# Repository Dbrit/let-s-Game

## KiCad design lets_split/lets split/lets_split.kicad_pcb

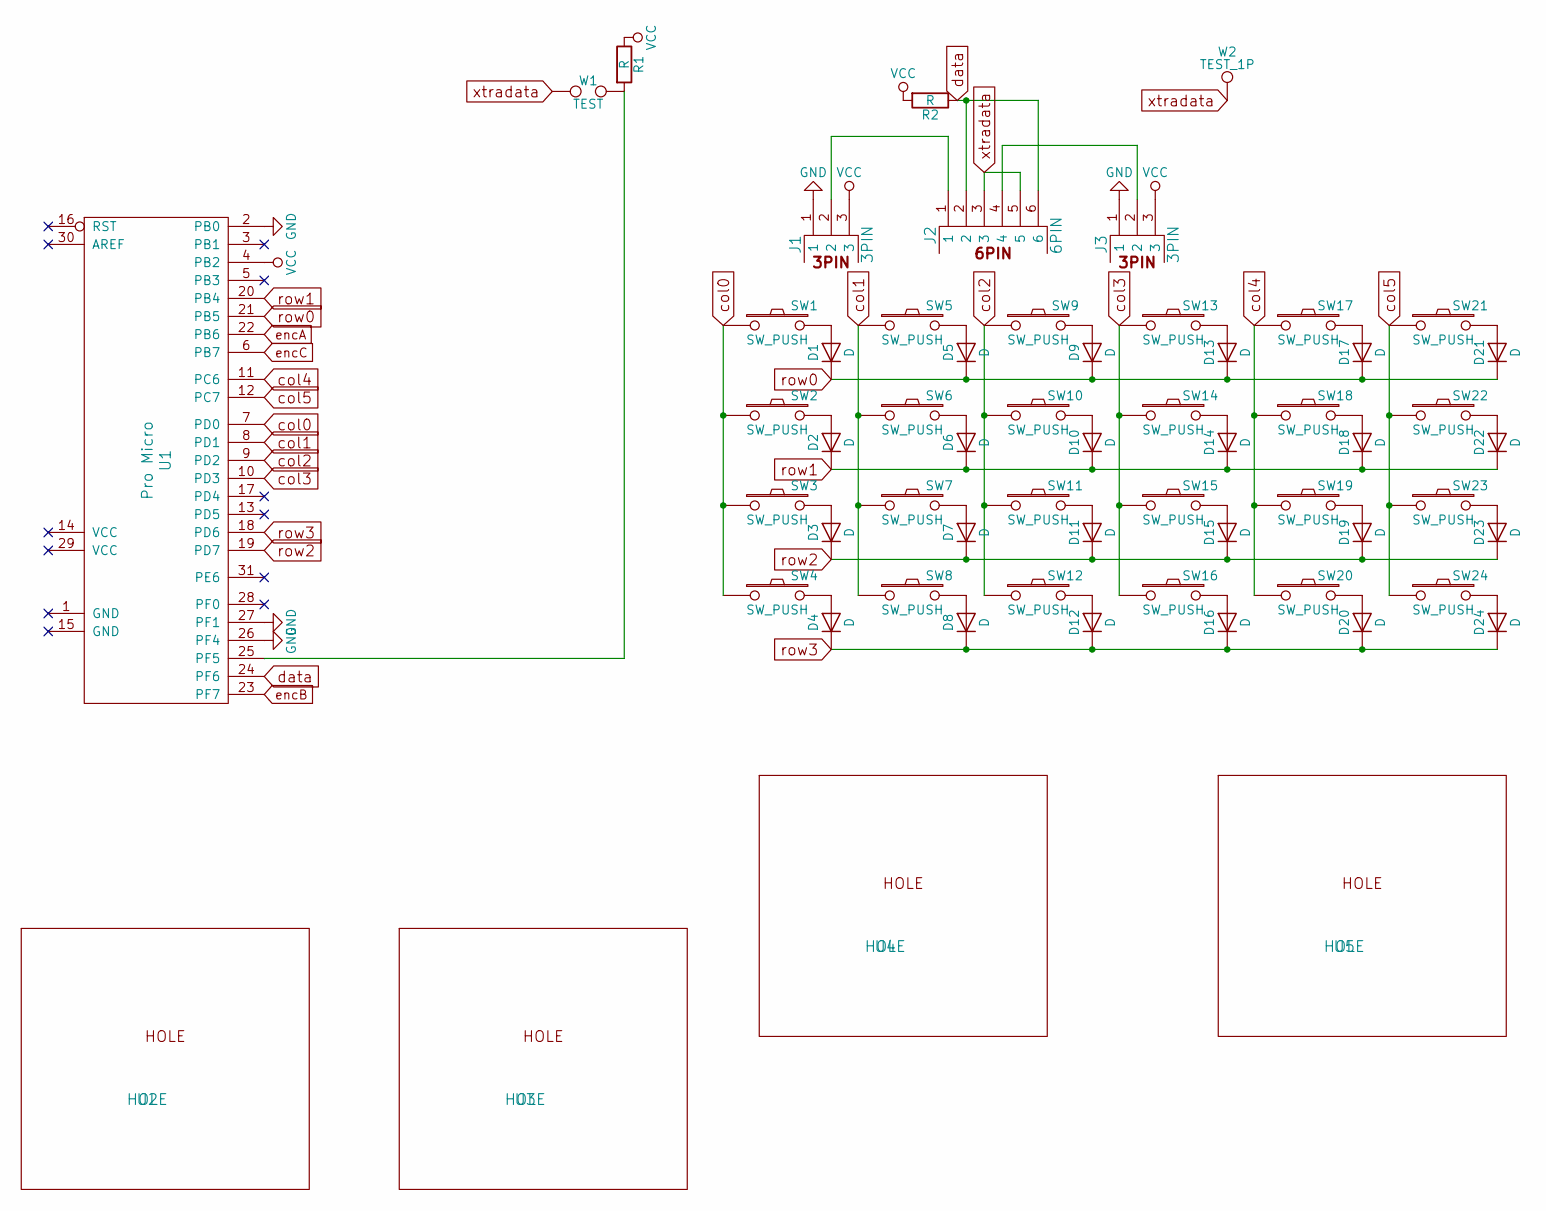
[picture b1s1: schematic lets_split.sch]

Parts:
D1, D2, D3, D4, D5, D6, D7, D8, D9, D10, D11, D12, D13, D14, D15, D16, D17, D18, D19, D20, D21, D22, D23, D24: D; Diode_DO-41_SOD81_Horizontal_RM10
J1, J3: 3PIN; jumper
J2: 6PIN; 4pin35mmAudio
R1, R2: R; RESISTOR
SW1, SW2, SW3, SW4, SW5, SW6, SW7, SW8, SW9, SW10, SW11, SW12, SW13, SW14, SW15, SW16, SW17, SW18, SW19, SW20, SW21, SW22, SW23, SW24: SW_PUSH; MXALPS_FLIP
U1: Pro Micro; ProMicro
U2, U3, U4, U5: HOLE
W1: TEST; JUMPER_SMD_2DUB
W2: TEST_1P; SolderWirePad_single_2mmDrill

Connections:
GND: J1.1, J3.1, U1.2 (PB0), U1.26 (PF4), U1.27 (PF1)
unnamed: D1.2 (A), SW1.2
unnamed: D2.2 (A), SW2.2
unnamed: D3.2 (A), SW3.2
unnamed: D4.2 (A), SW4.2
unnamed: D5.2 (A), SW5.2
unnamed: D6.2 (A), SW6.2
unnamed: D7.2 (A), SW7.2
unnamed: D8.2 (A), SW8.2
unnamed: D9.2 (A), SW9.2
unnamed: D10.2 (A), SW10.2
unnamed: D11.2 (A), SW11.2
unnamed: D12.2 (A), SW12.2
unnamed: D13.2 (A), SW13.2
unnamed: D14.2 (A), SW14.2
unnamed: D15.2 (A), SW15.2
unnamed: D16.2 (A), SW16.2
unnamed: D17.2 (A), SW17.2
unnamed: D18.2 (A), SW18.2
unnamed: D19.2 (A), SW19.2
unnamed: D20.2 (A), SW20.2
unnamed: D21.2 (A), SW21.2
unnamed: D22.2 (A), SW22.2
unnamed: D23.2 (A), SW23.2
unnamed: D24.2 (A), SW24.2
unnamed: J1.2, J2.1
unnamed: J2.4, J3.2
unnamed: R1.2, U1.25 (PF5), W1.2
VCC: J1.3, J3.3, R1.1, R2.2, U1.4 (PB2)
col0: SW1.1, SW2.1, SW3.1, SW4.1, U1.7 (PD0)
col1: SW5.1, SW6.1, SW7.1, SW8.1, U1.8 (PD1)
col2: SW9.1, SW10.1, SW11.1, SW12.1, U1.9 (PD2)
col3: SW13.1, SW14.1, SW15.1, SW16.1, U1.10 (PD3)
col4: SW17.1, SW18.1, SW19.1, SW20.1, U1.11 (PC6)
col5: SW21.1, SW22.1, SW23.1, SW24.1, U1.12 (PC7)
data: J2.2, J2.6, R2.1, U1.24 (PF6)
encA: U1.22 (PB6)
encB: U1.23 (PF7)
encC: U1.6 (PB7)
row0: D1.1 (K), D5.1 (K), D9.1 (K), D13.1 (K), D17.1 (K), D21.1 (K), U1.21 (PB5)
row1: D2.1 (K), D6.1 (K), D10.1 (K), D14.1 (K), D18.1 (K), D22.1 (K), U1.20 (PB4)
row2: D3.1 (K), D7.1 (K), D11.1 (K), D15.1 (K), D19.1 (K), D23.1 (K), U1.19 (PD7)
row3: D4.1 (K), D8.1 (K), D12.1 (K), D16.1 (K), D20.1 (K), D24.1 (K), U1.18 (PD6)
xtradata: J2.3, J2.5, W1.1, W2.1

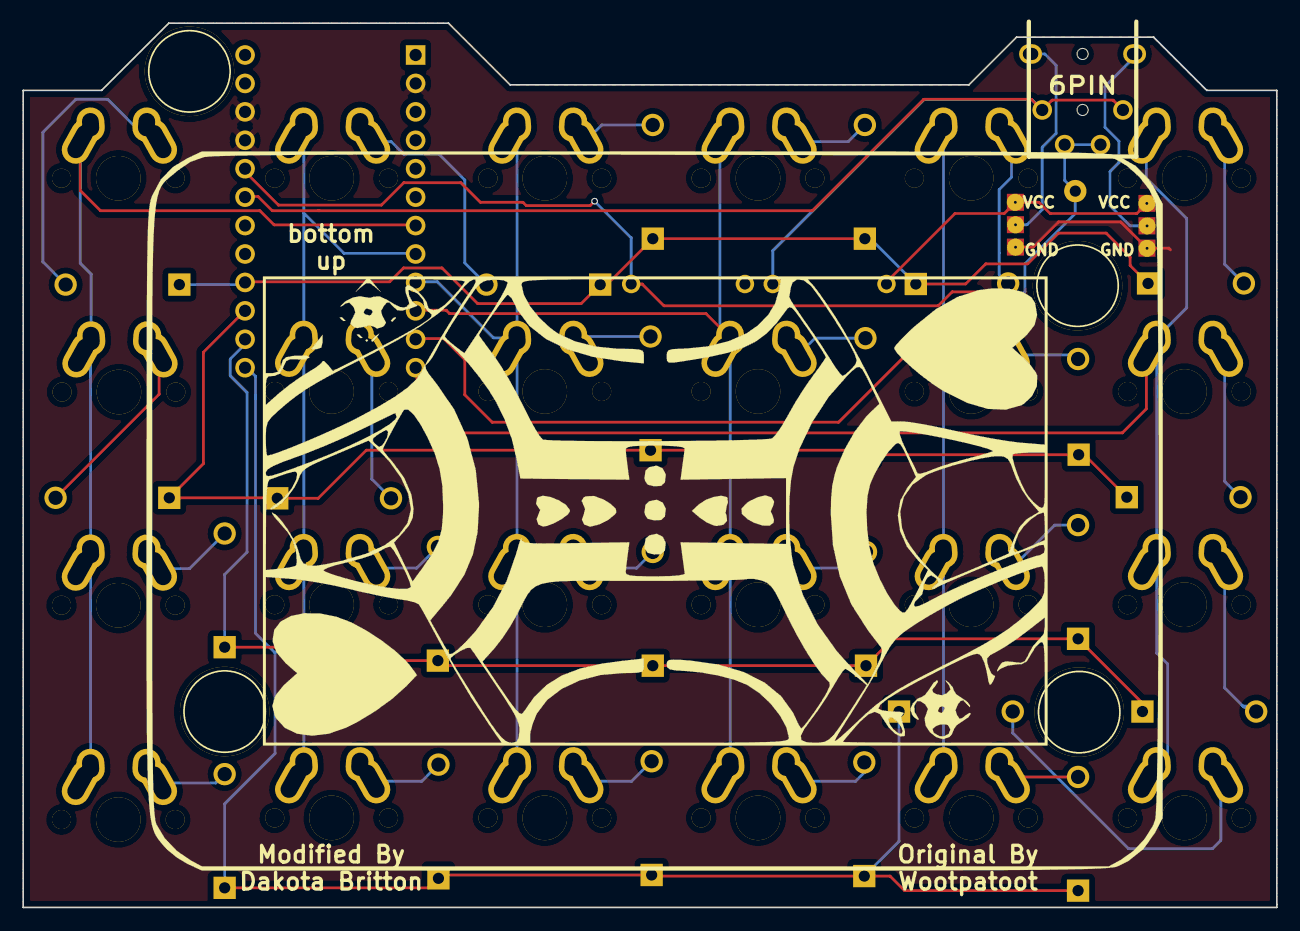
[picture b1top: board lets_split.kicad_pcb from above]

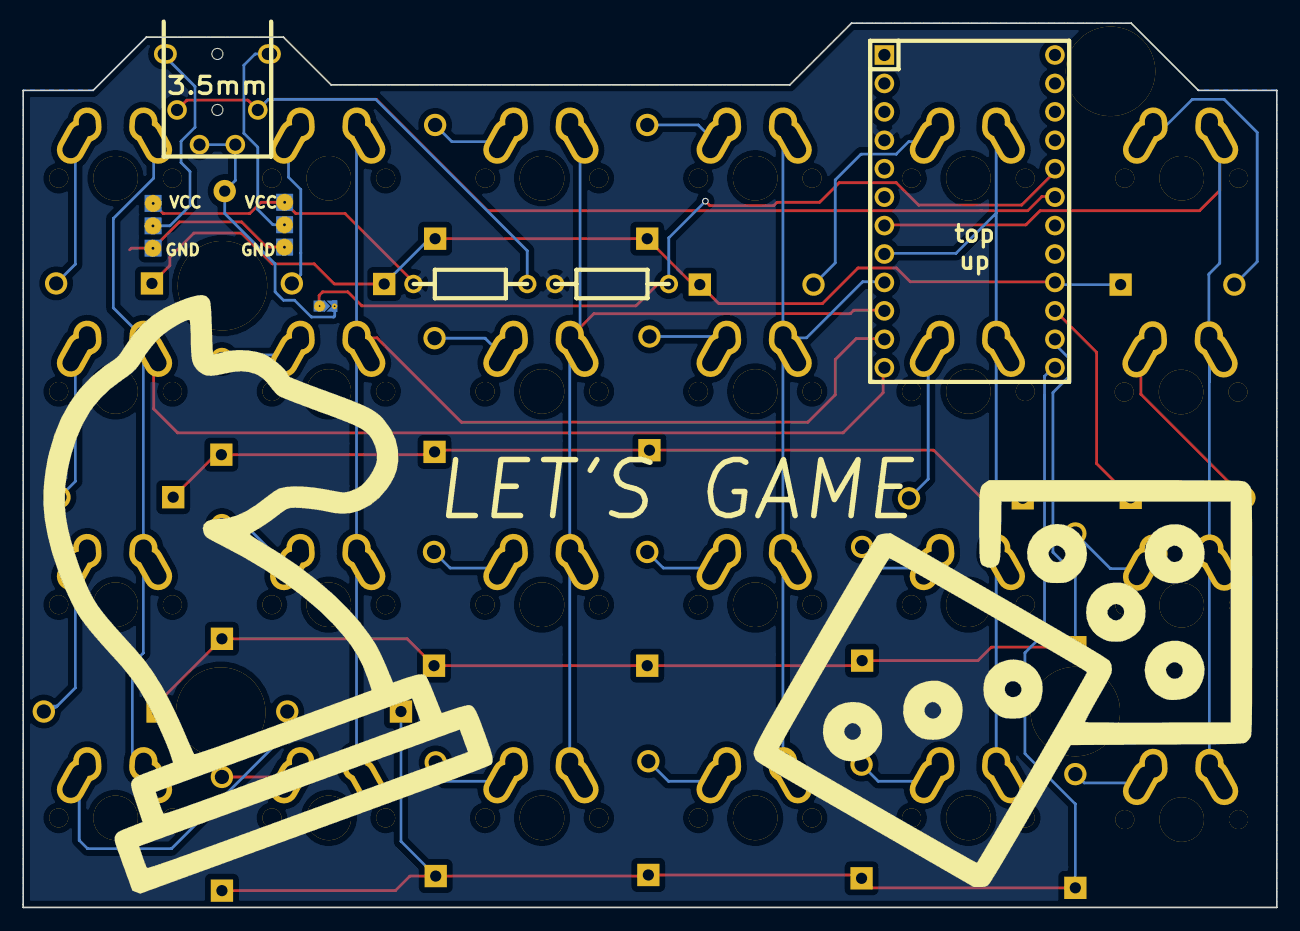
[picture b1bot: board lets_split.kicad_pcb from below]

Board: 2 copper layers, 112.0 x 79.0 mm, 60 parts (3 on the bottom side), 41 nets.

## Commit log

2020-12-30 Finished Rev1
2020-12-30 Added gerbers
2020-12-30 Updated PCB
